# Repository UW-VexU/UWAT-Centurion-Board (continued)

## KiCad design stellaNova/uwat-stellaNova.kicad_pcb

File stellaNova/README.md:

# uwat-stellaNova, rev A

stellaNova is a VEX V5 wireless debugger. Full name: uwat-stellaNova.

It is an ESP32-S3 board that plugs into one VEX V5 smart port, receives whatever the brain writes to that port
over RS-485, and serves it to a laptop, phone or tablet over WiFi or Bluetooth LE. It can also send
commands back to the brain over the same wire (half duplex). Powered from the V5 battery through the
smart port, or from USB-C on the bench.

## What is in this folder

- The KiCad project is in this folder: open `uwat-stellaNova.kicad_pro` in KiCad 10. The project symbols
  (`stellaNova.kicad_sym`), footprints (`stellaNova.pretty/`) and 3D models (`3dmodels/`) are here too.
- `archive/uwat-stellaNova-4layer.kicad_pcb`: the original 4-layer board, kept for reference.
- `fabrication/`: **still the old 4-layer outputs. Regenerate the gerbers, drill and placement files from the 2-layer
  board before ordering.** `gerbers/` holds the files unzipped, plus the drill map PDFs.
- `bom/`: `uwat-stellaNova_revA_BOM.xlsx` (prices, order quantities, notes), `uwat-stellaNova_revA_DigiKey_upload.csv`
  (upload in DigiKey BOM Manager), plus a plain CSV BOM and a JLCPCB-style BOM.
- `docs/`: schematic PDF and PNG, layout, assembly and 3D renders, and a STEP model of the assembled board.
  The layout and 3D renders still show the 4-layer board.
- `AUDIT.md`: design audit results. `generator-scripts/`: the scripts that built the design, for reference only.

## Ordering the PCB

- Regenerate the gerbers first (see `fabrication/` above). Layers: 2. Thickness: 1.6 mm. Copper: 1 oz.
- No impedance control needed. USB here is full speed.
- Min track/spacing: the board uses 0.15 mm gaps, so pick 5/5 mil (0.127 mm) or finer.
- Min hole: 0.2 mm. The ESP32 module footprint has 0.2 mm thermal vias. Normal vias are 0.3 mm.
- Surface finish: lead-free HASL works. ENIG gives flatter pads for the ESP32 module and USB-C if hand soldering.
- Any solder mask color. Vias are tented in the files.

## Back of the board

The back reads STELLANOVA, then UWAT-VEXU F26, in Chakra Petch Bold. The font is embedded in the board
file, so the gerbers come out the same on any computer. The test pads keep their labels: TX0, RX0, VIN,
GND and 3V3, plus V5 PORT at the jack.

These notes used to be printed on the back. They live here now.

- Board: uwat-stellaNova, rev A.
- Smart port pins: 1 = A, 2 = B, 3 = GND, 4 = VBAT.
- Main parts: ESP32-S3, USB-C, RS-485.

## Board

- 48 x 40 mm, 2 layers, 1.6 mm FR4. Both layers carry signals and a GND pour. 3.3 V runs as a 0.3 mm trace,
  mostly on the back, from L1 to every 3.3 V pin. Rev A was first laid out on 4 layers with inner GND and 3.3 V
  planes. See AUDIT.md for the conversion.
- ESP32 antenna overhangs the top edge by 6 mm (Espressif's preferred placement). Keep metal 15 mm away.
- No mounting holes. The board hangs from its smart cable.
- All parts on the top side, so single-sided assembly. Test pads are on the back.
- USB-C alone gives the 500 mA USB 2.0 default. Worst case the board draws about 480 mA from it,
  so use a powered hub or the brain for long WiFi sessions. R22 keeps VBUS at 0 V on port power
  so a laptop still attaches when plugged in later.
- D5 (USB ESD protection) has its supply pin, pin 5, on 3.3 V rather than VBUS. So on port power the
  ESP32's D+ pull-up cannot lift VBUS through D5. USB and the smart cable can go in either order.
- C6 (220 uF bulk) is not fitted: the buck datasheet characterises 22 to 68 uF of output
  capacitance. Fit it only if a load-step test shows a dip on 3.3 V.

- U3 is MAX33071EASA+: its A/B pins survive +/-65 V even unpowered, so a miswired or damaged
  smart cable cannot kill it. ST3485EBDR (497-2080-1-ND, about $2.49) is a cheaper drop-in with
  the same pinout, but its bus pins are only rated 14 V.
- J1 pin field: other nets keep 0.5 mm from J1's pins (custom rule in the .kicad_dru), so a solder
  bridge on the hand-soldered jack cannot reach USB or a GPIO.
- Battery copper (VBAT_PORT and the fuse to diode link) keeps 0.5 mm from every other net ("Battery"
  net class), so a bridge or debris cannot put 14 V on an ESP32 pin.
- 3.3 V buck: the 10 uF input cap sits right across the U2 VIN and GND pins, the switch node runs
  straight out to L1, and the output caps sit next to L1. Feedback is on the far side, away from SW.
- SW1 (RESET) and SW2 (BOOT) are C&K PTS810 push buttons. Per the datasheet, pins 1 and 2 are tied
  together, pins 3 and 4 are tied together, and pressing the button joins the two pairs. The
  footprint and wiring match that.
- Do not populate parts (C6, R2, R4) have no paste openings and are left out of the placement file.
- Expansion pins: J4 (SDA on IO37, SCL on IO35), J5 (GND) and J6 (3.3 V) are 2.54 mm through-hole pins between
  the ESP32 and the microSD socket, labelled on the top silkscreen. Use them for an I2C sensor or display, or as
  UART1. Cut 4 pins from a breakaway strip and solder them when needed. The board has no I2C pull-ups. Most I2C
  breakout boards include them. If yours does not, add 4.7 k from SDA and from SCL to 3.3 V.

## Things to know when writing firmware or using it

- RS-485 echo: the receiver is always on (RE tied low), so the ESP32 hears its own transmissions on
  RX. Throw away the echoed bytes after each send, or use them to check for bus collisions.
- IO39 to IO42 go to the microSD card, so pin JTAG is not available. Use the built in USB JTAG.

## If you use JLCPCB assembly

- The BOM lists DigiKey parts. Match each line to an LCSC part in the JLCPCB tool, or hand solder.
- Check every part rotation in the JLCPCB placement preview. KiCad and JLCPCB do not always agree
  on the zero angle, especially for the ESP32 module, USB-C, the diodes and the LEDs.
- J1 (smart port jack) is through-hole. Hand solder it after assembly.

## Check before first power-up

0. Before ordering, print `docs/uwat-stellaNova-1to1-print.pdf` at 100% scale (not "fit to page")
   and set a real Molex 0955012441 jack on it (the same jack as powerJackal). Its pins and the two pegs
   must line up with the holes. If a peg does not fit, it only locates the jack, so it can be cut off.
1. Jack pin map: 1 = RS-485 A, 2 = RS-485 B, 3 = GND, 4 = battery. Contact order is A, B, GND, + as
   on the labelled smart cable photo on the VEX Forum (black A, red B, green GND, yellow +).
   VEX smart cables are straight-through.
2. On the first board, plug a smart cable into J1 and beep each wire through to the pads on the back:
   black to J1.1, red to J1.2, green to J1.3, yellow to J1.4. Also beep each button: SW1 should
   short EN to GND only while pressed, SW2 should short IO0 to GND only while pressed.
3. Power from USB-C first: 3.3 V on TP2. Then plug into the brain with USB unplugged. The PWR LED
   should light. If it does not, unplug: nothing is damaged (D2 blocks reverse, U3 is 65 V rated).
4. Scope A/B during bring-up and confirm the brain releases the bus between transmissions.
5. Load-step 3.3 V (50 to 400 mA) at 10 V and 14.6 V in. Fit C6 only if it dips.

## Firmware pin map

| Function | GPIO |
|---|---|
| RS-485 RX / DE / TX | IO9 / IO10 / IO11 (UART RS485 half-duplex mode, RTS = IO10) |
| USB D- / D+ | IO19 / IO20 (USB Serial/JTAG) |
| microSD CLK / CMD / D0 / D1 / D2 / D3 | IO40 / IO41 / IO39 / IO38 / IO2 / IO42 |
| microSD card detect | IO1 (low = card in) |
| LEDs LINK / ACT | IO13 / IO14 (high = on) |
| BOOT / RESET | IO0 / EN |
| UART0 TX / RX (back pads) | IO43 / IO44 |
| Expansion pins J4 SDA / SCL | IO37 / IO35 (any function, so they also work as UART1 TX / RX) |
| Expansion pins J5 / J6 | GND / 3.3 V |

Module is ESP32-S3-WROOM-1-N16R2: set PSRAM to Quad (QSPI) mode, not Octal. IO35 and IO37 are free only
because this module's PSRAM is quad. A module with octal PSRAM (R8 or R16V) uses those pins, so keep the N16R2.

Brain side: `vexGenericSerialEnable(port, 0)` then `vexGenericSerialBaudrate(port, 230400)`, or `pros::Serial`.

## Verification

2-layer board, checked with KiCad 10 on 2026-10-30. The report is `uwat-stellaNova-drc.rpt`.

- ERC: 0 errors.
- PCB DRC, with the J1 pin-field rule and the 0.5 mm battery rule: 0 violations, 0 unconnected.
- Schematic to PCB parity: 0 issues. Every pad is on the net the schematic gives it.
- The board file is KiCad 10 format, so KiCad 9 and older cannot open it. The schematic is still KiCad 7 format.

## BOM (DigiKey Canada, checked 2026-10-30)

| Qty | Refs | Value | MPN | DigiKey CA | Stock | CAD qty 1 |
|---|---|---|---|---|---|---|
| 1 | C1 | 10uF 50V | Samsung CL32B106KBJNNNE | 1276-3387-1-ND | 742,985 | $1.02 |
| 5 | C2 C3 C7 C9 C12 | 100nF | Yageo CC0603KRX7R9BB104 | 311-1344-1-ND | 4,044,224 | $0.21 |
| 2 | C4 C5 | 22uF | Murata GRM21BR61A226ME51L | 490-10511-1-ND | 269,759 | $0.30 |
| 2 | C8 C11 | 10uF | Murata GRM21BR61E106KA73K | 490-16824-1-ND | 88,143 | $0.25 |
| 1 | C10 | 1uF | TDK C1608X5R1H105K080AB | 445-7468-1-ND | 105,003 | $0.25 |
| 1 | C13 | 56pF | KEMET C0603C560J5GACTU | 399-C0603C560J5GACTUCT-ND | 153,858 | $0.15 |
| 1 | D1 | SMAJ18A | Bourns SMAJ18A | SMAJ18ABCT-ND | 29,489 | $0.77 |
| 2 | D2 D3 | PMEG6020ER | Nexperia PMEG6020ER,115 | 1727-5217-1-ND | 375,398 | $0.74 |
| 1 | D5 | USBLC6-2SC6 | STMicroelectronics USBLC6-2SC6 | 497-5235-1-ND | 63,343 | $0.80 |
| 1 | D6 | Green | Lite-On LTST-C191KGKT | 160-1446-1-ND | 2,712,898 | $0.24 |
| 1 | D7 | Orange | Lite-On LTST-C191KFKT | 160-1445-1-ND | 195,728 | $0.22 |
| 1 | D8 | Red | Lite-On LTST-C191KRKT | 160-1447-1-ND | 1,354,761 | $0.24 |
| 1 | F1 | PTC 0.5 A 30 V | Bel Fuse 0ZCG0050AF2C | 5923-0ZCG0050AF2CCT-ND | 345,670 | $0.31 |
| 1 | J1 | V5 smart port (4P4C) | Molex 0955012441 | WM5568-ND | 4,151 | $1.53 |
| 1 | J2 | USB-C 2.0 | GCT USB4105-GF-A | 2073-USB4105-GF-ACT-ND | 85,103 | $1.19 |
| 1 | J3 | microSD push-push | Hirose DM3AT-SF-PEJM5 | HR1964CT-ND | 76,375 | $5.27 |
| 1 | L1 | 10uH | Wurth 74438357100 | 732-11206-1-ND | 15,980 | $2.68 |
| 1 | R1 | 100k | Stackpole RMCF0603FT100K | RMCF0603FT100KCT-ND | 970,951 | $0.17 |
| 9 | R3 R5 R6 R9 R10 R11 R12 R13 R14 | 10k | Yageo RC0603FR-1310KL | 13-RC0603FR-1310KLCT-ND | 221,620 | $0.16 |
| 3 | R7 R8 R22 | 5.1k | Yageo RC0603FR-075K1L | 311-5.10KHRCT-ND | 405,843 | $0.16 |
| 3 | R15 R16 R17 | 1k | Yageo RC0603FR-071KL | 311-1.00KHRCT-ND | 1,993,948 | $0.17 |
| 2 | R18 R19 | 22 | Stackpole RMCF0603FT22R0 | RMCF0603FT22R0CT-ND | 2,171,898 | $0.16 |
| 1 | R20 | 93.1k | Stackpole RMCF0603FT93K1 | RMCF0603FT93K1CT-ND | 216,165 | $0.16 |
| 1 | R21 | 30.1k | Yageo RC0603FR-0730K1L | 311-30.1KHRCT-ND | 119,797 | $0.16 |
| 2 | SW1 SW2 | Tactile | C&K PTS810 SJM 250 SMTR LFS | CKN10502CT-ND | 69,851 | $0.92 |
| 1 | U1 | ESP32-S3-WROOM-1-N16R2 | Espressif ESP32-S3-WROOM-1-N16R2 | 5407-ESP32-S3-WROOM-1-N16R2CT-ND | 4,702 | $10.61 |
| 1 | U2 | AP63301WU-7 | Diodes Inc AP63301WU-7 | 31-AP63301WU-7CT-ND | 13,846 | $1.52 |
| 1 | U3 | MAX33071EASA+ | Analog Devices MAX33071EASA+ | 505-MAX33071EASA+-ND | 2,956 | $12.30 |
| 4 pins | J4 J5 J6 | Header pins, 2.54 mm | Sullins PRPC040SAAN-RC (40-pin strip, one covers 10 boards) | S1011EC-40-ND | 65,709 | $1.83 per strip |

Do not populate: C6 R2 R4

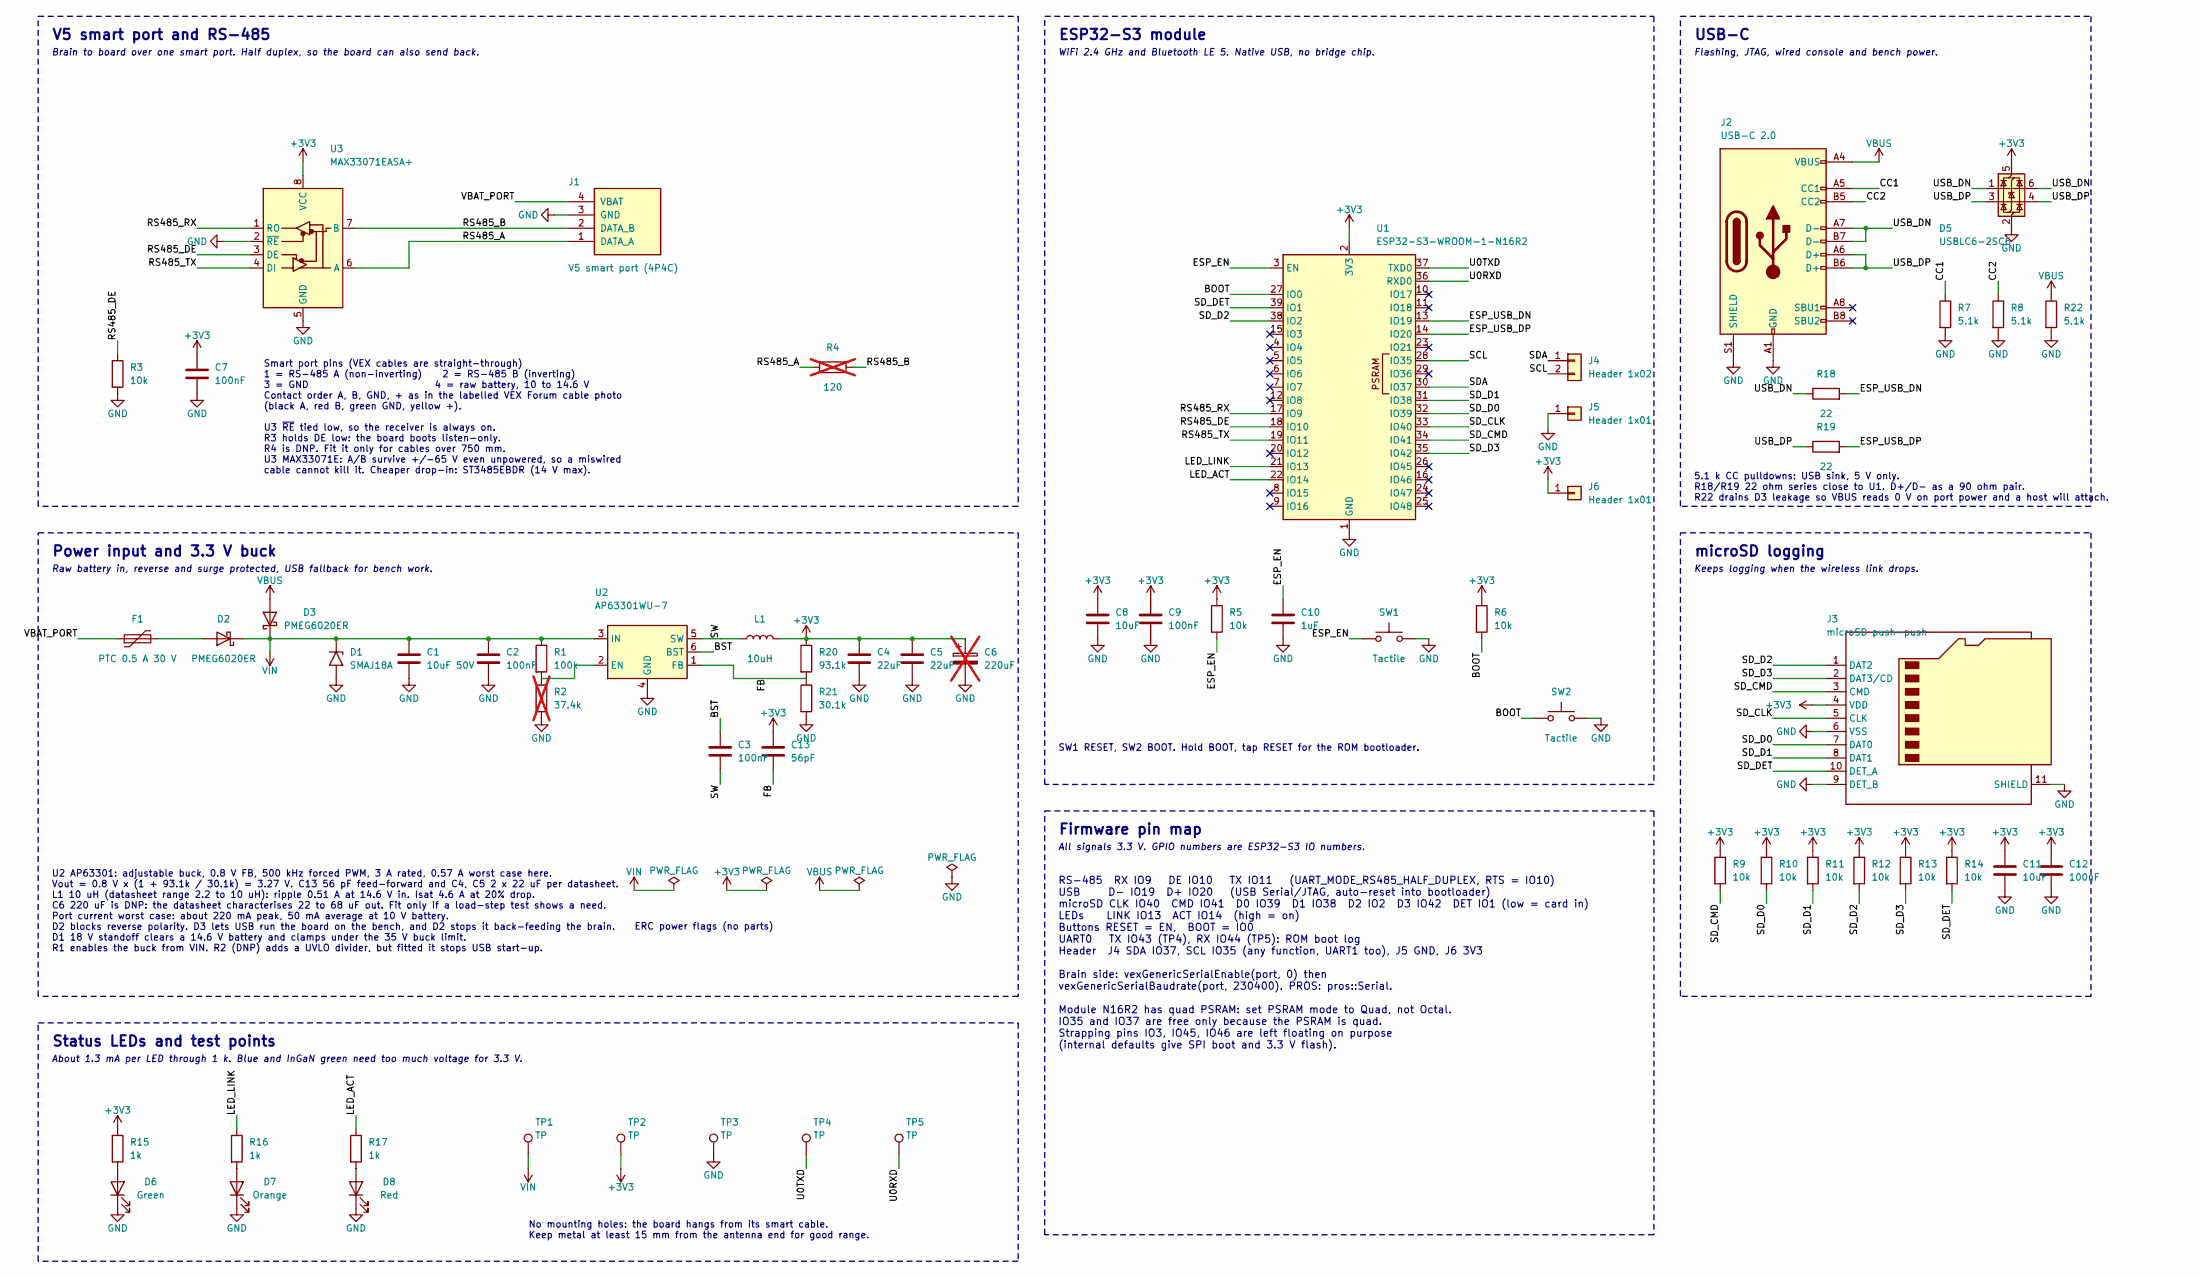
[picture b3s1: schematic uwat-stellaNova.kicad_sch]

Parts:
C1: 10uF 50V; C_1210_3225Metric; MPN CL32B106KBJNNNE; DigiKey 1276-3387-1-ND
C2, C3, C7, C9, C12: 100nF; C_0603_1608Metric; MPN CC0603KRX7R9BB104; DigiKey 311-1344-1-ND
C4, C5: 22uF; C_0805_2012Metric; MPN GRM21BR61A226ME51L; DigiKey 490-10511-1-ND
C6: 220uF; CP_EIA-3528-21_Kemet-B; MPN T520B227M006ATE045; DigiKey 399-5755-1-ND; not fitted
C8, C11: 10uF; C_0805_2012Metric; MPN GRM21BR61E106KA73K; DigiKey 490-16824-1-ND
C10: 1uF; C_0603_1608Metric; MPN C1608X5R1H105K080AB; DigiKey 445-7468-1-ND
C13: 56pF; C_0603_1608Metric; MPN C0603C560J5GACTU; DigiKey 399-C0603C560J5GACTUCT-ND
D1: SMAJ18A; D_SMA; MPN SMAJ18A; DigiKey SMAJ18ABCT-ND
D2, D3: PMEG6020ER; Nexperia_CFP3_SOD-123W; MPN PMEG6020ER,115; DigiKey 1727-5217-1-ND
D5: USBLC6-2SC6; SOT-23-6; MPN USBLC6-2SC6; DigiKey 497-5235-1-ND
D6: Green; LED_0603_1608Metric; MPN LTST-C191KGKT; DigiKey 160-1446-1-ND
D7: Orange; LED_0603_1608Metric; MPN LTST-C191KFKT; DigiKey 160-1445-1-ND
D8: Red; LED_0603_1608Metric; MPN LTST-C191KRKT; DigiKey 160-1447-1-ND
F1: PTC 0.5 A 30 V; Fuse_1812_4532Metric; MPN 0ZCG0050AF2C; DigiKey 5923-0ZCG0050AF2CCT-ND
J1: V5 smart port (4P4C); Molex_95501-2441_4P4C_Horizontal; MPN 0955012441; DigiKey WM5568-ND
J2: USB-C 2.0; USB_C_Receptacle_GCT_USB4105-xx-A_16P_TopMnt_Horizontal; MPN USB4105-GF-A; DigiKey 2073-USB4105-GF-ACT-ND
J3: microSD push-push; microSD_HC_Hirose_DM3AT-SF-PEJM5; MPN DM3AT-SF-PEJM5; DigiKey HR1964CT-ND
J4: Header 1x02; PinHeader_1x02_P2.54mm_Vertical_Compact; MPN PRPC040SAAN-RC; DigiKey S1011EC-40-ND
J5, J6: Header 1x01; PinHeader_1x01_P2.54mm_Vertical_Compact; MPN PRPC040SAAN-RC; DigiKey S1011EC-40-ND
L1: 10uH; L_Wuerth_MAPI-4030; MPN 74438357100; DigiKey 732-11206-1-ND
R1: 100k; R_0603_1608Metric; MPN RMCF0603FT100K; DigiKey RMCF0603FT100KCT-ND
R2: 37.4k; R_0603_1608Metric; MPN RC0603FR-0737K4L; DigiKey 311-37.4KHRCT-ND; not fitted
R3, R5, R6, R9, R10, R11, R12, R13, R14: 10k; R_0603_1608Metric; MPN RC0603FR-1310KL; DigiKey 13-RC0603FR-1310KLCT-ND
R4: 120; R_0603_1608Metric; MPN RC0603FR-07120RL; DigiKey 311-120HRCT-ND; not fitted
R7, R8, R22: 5.1k; R_0603_1608Metric; MPN RC0603FR-075K1L; DigiKey 311-5.10KHRCT-ND
R15, R16, R17: 1k; R_0603_1608Metric; MPN RC0603FR-071KL; DigiKey 311-1.00KHRCT-ND
R18, R19: 22; R_0603_1608Metric; MPN RMCF0603FT22R0; DigiKey RMCF0603FT22R0CT-ND
R20: 93.1k; R_0603_1608Metric; MPN RMCF0603FT93K1; DigiKey RMCF0603FT93K1CT-ND
R21: 30.1k; R_0603_1608Metric; MPN RC0603FR-0730K1L; DigiKey 311-30.1KHRCT-ND
SW1, SW2: Tactile; SW_SPST_PTS810; MPN PTS810 SJM 250 SMTR LFS; DigiKey CKN10502CT-ND
TP1, TP2, TP3, TP4, TP5: TP; TestPoint_Pad_D1.5mm
U1: ESP32-S3-WROOM-1-N16R2; ESP32-S3-WROOM-1; MPN ESP32-S3-WROOM-1-N16R2; DigiKey 5407-ESP32-S3-WROOM-1-N16R2CT-ND
U2: AP63301WU-7; TSOT-23-6; MPN AP63301WU-7; DigiKey 31-AP63301WU-7CT-ND
U3: MAX33071EASA+; SOIC-8_3.9x4.9mm_P1.27mm; MPN MAX33071EASA+; DigiKey 505-MAX33071EASA+-ND

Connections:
+3V3: C4.1, C5.1, C6.1, C7.1, C8.1, C9.1, C11.1, C12.1, C13.1, D5.5 (VBUS), J3.4 (VDD), J6.1, L1.2, R5.1, R6.1, R9.1, R10.1, R11.1, R12.1, R13.1, R14.1, R15.1, R20.1, TP2.1, U1.2 (3V3), U3.8 (VCC)
/BOOT: R6.2, SW2.1, U1.27 (IO0)
/BST: C3.1, U2.6 (BST)
/CC1: J2.A5 (CC1), R7.1
/CC2: J2.B5 (CC2), R8.1
/ESP_EN: C10.1, R5.2, SW1.1, U1.3 (EN)
/ESP_USB_DN: R18.2, U1.13 (IO19)
/ESP_USB_DP: R19.2, U1.14 (IO20)
/FB: C13.2, R20.2, R21.1, U2.1 (FB)
/LED_ACT: R17.1, U1.22 (IO14)
/LED_LINK: R16.1, U1.21 (IO13)
/RS485_A: J1.1 (DATA_A), R4.1, U3.6 (A)
/RS485_B: J1.2 (DATA_B), R4.2, U3.7 (B)
/RS485_DE: R3.1, U1.18 (IO10), U3.3 (DE)
/RS485_RX: U1.17 (IO9), U3.1 (RO)
/RS485_TX: U1.19 (IO11), U3.4 (DI)
/SCL: J4.2, U1.28 (IO35)
/SDA: J4.1, U1.30 (IO37)
/SD_CLK: J3.5 (CLK), U1.33 (IO40)
/SD_CMD: J3.3 (CMD), R9.2, U1.34 (IO41)
/SD_D0: J3.7 (DAT0), R10.2, U1.32 (IO39)
/SD_D1: J3.8 (DAT1), R11.2, U1.31 (IO38)
/SD_D2: J3.1 (DAT2), R12.2, U1.38 (IO2)
/SD_D3: J3.2 (DAT3/CD), R13.2, U1.35 (IO42)
/SD_DET: J3.10 (DET_A), R14.2, U1.39 (IO1)
/SW: C3.2, L1.1, U2.5 (SW)
/U0RXD: TP5.1, U1.36 (RXD0)
/U0TXD: TP4.1, U1.37 (TXD0)
/USB_DN: D5.1 (I/O1), D5.6 (I/O1), J2.A7 (D-), J2.B7 (D-), R18.1
/USB_DP: D5.3 (I/O2), D5.4 (I/O2), J2.A6 (D+), J2.B6 (D+), R19.1
/VBAT_PORT: F1.1, J1.4 (VBAT)
GND: C1.2, C2.2, C4.2, C5.2, C6.2, C7.2, C8.2, C9.2, C10.2, C11.2, C12.2, D1.2 (A2), D5.2 (GND), D6.1 (K), D7.1 (K), D8.1 (K), J1.3 (GND), J2.A1 (GND), J2.A12 (GND), J2.B1 (GND), J2.B12 (GND), J2.S1 (SHIELD), J3.6 (VSS), J3.9 (DET_B), J3.11 (SHIELD), J5.1, R2.2, R3.2, R7.2, R8.2, R21.2, R22.2, SW1.2, SW2.2, TP3.1, U1.1 (GND), U1.40 (GND), U1.41 (GND), U2.4 (GND), U3.2 (~RE), U3.5 (GND)
unnamed: D2.2 (A), F1.2
unnamed: D6.2 (A), R15.2
unnamed: D7.2 (A), R16.2
unnamed: D8.2 (A), R17.2
unnamed: R1.2, R2.1, U2.2 (EN)
VBUS: D3.2 (A), J2.A4 (VBUS), J2.A9 (VBUS), J2.B4 (VBUS), J2.B9 (VBUS), R22.1
VIN: C1.1, C2.1, D1.1 (A1), D2.1 (K), D3.1 (K), R1.1, TP1.1, U2.3 (IN)

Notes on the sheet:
V5 smart port and RS-485
Brain to board over one smart port. Half duplex, so the board can also send back.
Smart port pins (VEX cables are straight-through) 1 = RS-485 A (non-inverting) 2 = RS-485 B (inverting) 3 = GND 4 = raw battery, 10 to 14.6 V Contact order A, B, GND, + as in the labelled VEX Forum cable photo (black A, red B, green GND, yellow +). U3 ~{RE} tied low, so the receiver is always on. R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
Power input and 3.3 V buck
Raw battery in, reverse and surge protected, USB fallback for bench work.
ERC power flags (no parts)
U2 AP63301: adjustable buck, 0.8 V FB, 500 kHz forced PWM, 3 A rated, 0.57 A worst case here. Vout = 0.8 V x (1 + 93.1k / 30.1k) = 3.27 V. C13 56 pF feed-forward and C4, C5 2 x 22 uF per datasheet. L1 10 uH (datasheet range 2.2 to 10 uH): ripple 0.51 A at 14.6 V in. Isat 4.6 A at 20% drop. C6 220 u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
ESP32-S3 module
WiFi 2.4 GHz and Bluetooth LE 5. Native USB, no bridge chip.
SW1 RESET, SW2 BOOT. Hold BOOT, tap RESET for the ROM bootloader.
USB-C
Flashing, JTAG, wired console and bench power.
5.1 k CC pulldowns: USB sink, 5 V only. R18/R19 22 ohm series close to U1. D+/D- as a 90 ohm pair. R22 drains D3 leakage so VBUS reads 0 V on port power and a host will attach.
microSD logging
Keeps logging when the wireless link drops.
Status LEDs and test points
About 1.3 mA per LED through 1 k. Blue and InGaN green need too much voltage for 3.3 V.
No mounting holes: the board hangs from its smart cable. Keep metal at least 15 mm from the antenna end for good range.
Firmware pin map
All signals 3.3 V. GPIO numbers are ESP32-S3 IO numbers.
RS-485 RX IO9 DE IO10 TX IO11 (UART_MODE_RS485_HALF_DUPLEX, RTS = IO10) USB D- IO19 D+ IO20 (USB Serial/JTAG, auto-reset into bootloader) microSD CLK IO40 CMD IO41 D0 IO39 D1 IO38 D2 IO2 D3 IO42 DET IO1 (low = card in) LEDs LINK IO13 ACT IO14 (high = on) Buttons RESET = EN, BOOT = IO0 UART0 TX IO43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

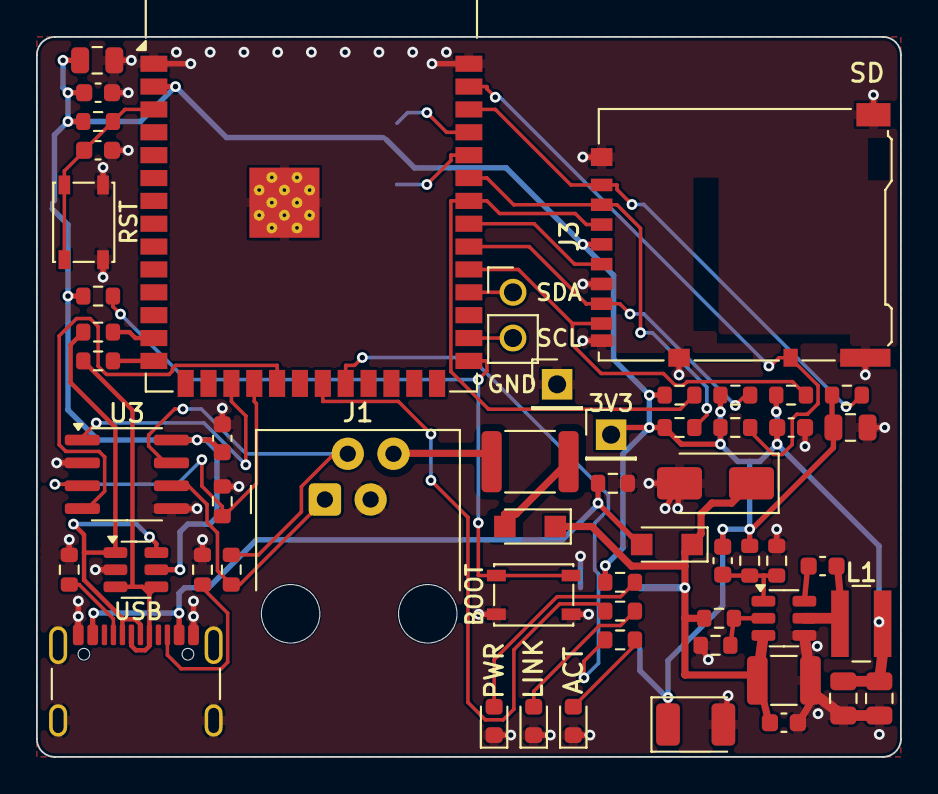
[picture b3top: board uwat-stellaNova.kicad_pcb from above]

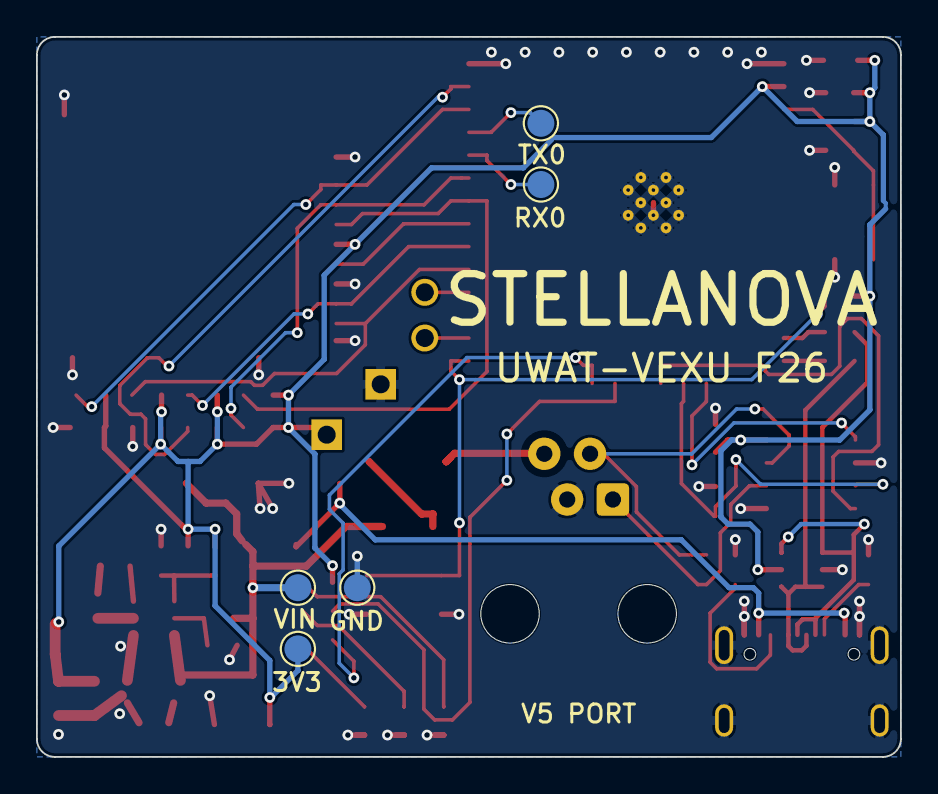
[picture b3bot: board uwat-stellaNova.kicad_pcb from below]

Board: 2 copper layers, 48.0 x 40.0 mm, 60 parts (5 on the bottom side), 39 nets.

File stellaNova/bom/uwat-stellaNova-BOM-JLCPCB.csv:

Comment,Designator,Footprint,MPN
10uF 50V,C1,C_1210_3225Metric,CL32B106KBJNNNE
100nF,"C2,C3,C7,C9,C12",C_0603_1608Metric,CC0603KRX7R9BB104
22uF,"C4,C5",C_0805_2012Metric,GRM21BR61A226ME51L
10uF,"C8,C11",C_0805_2012Metric,GRM21BR61E106KA73K
1uF,C10,C_0603_1608Metric,C1608X5R1H105K080AB
56pF,C13,C_0603_1608Metric,C0603C560J5GACTU
SMAJ18A,D1,D_SMA,SMAJ18A
PMEG6020ER,"D2,D3",Nexperia_CFP3_SOD-123W,"PMEG6020ER,115"
USBLC6-2SC6,D5,SOT-23-6,USBLC6-2SC6
Green,D6,LED_0603_1608Metric,LTST-C191KGKT
Orange,D7,LED_0603_1608Metric,LTST-C191KFKT
Red,D8,LED_0603_1608Metric,LTST-C191KRKT
PTC 0.5 A 30 V,F1,Fuse_1812_4532Metric,0ZCG0050AF2C
V5 smart port (4P4C),J1,Molex_95501-2441_4P4C_Horizontal,0955012441
USB-C 2.0,J2,USB_C_Receptacle_GCT_USB4105-xx-A_16P_TopMnt_Horizontal,USB4105-GF-A
microSD push-push,J3,microSD_HC_Hirose_DM3AT-SF-PEJM5,DM3AT-SF-PEJM5
10uH,L1,L_Wuerth_MAPI-4030,74438357100
100k,R1,R_0603_1608Metric,RMCF0603FT100K
10k,"R3,R5,R6,R9,R10,R11,R12,R13,R14",R_0603_1608Metric,RC0603FR-1310KL
5.1k,"R7,R8,R22",R_0603_1608Metric,RC0603FR-075K1L
1k,"R15,R16,R17",R_0603_1608Metric,RC0603FR-071KL
22,"R18,R19",R_0603_1608Metric,RMCF0603FT22R0
93.1k,R20,R_0603_1608Metric,RMCF0603FT93K1
30.1k,R21,R_0603_1608Metric,RC0603FR-0730K1L
Tactile,"SW1,SW2",SW_SPST_PTS810,PTS810 SJM 250 SMTR LFS
ESP32-S3-WROOM-1-N16R2,U1,ESP32-S3-WROOM-1,ESP32-S3-WROOM-1-N16R2
AP63301WU-7,U2,TSOT-23-6,AP63301WU-7
MAX33071EASA+,U3,SOIC-8_3.9x4.9mm_P1.27mm,MAX33071EASA+
Header 1x02,J4,PinHeader_1x02_P2.54mm_Vertical_Compact,PRPC040SAAN-RC
Header 1x01,"J5,J6",PinHeader_1x01_P2.54mm_Vertical_Compact,PRPC040SAAN-RC

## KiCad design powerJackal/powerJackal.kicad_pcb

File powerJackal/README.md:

# powerJackal: smart port power test board, rev A

A small test board for the UWAT VEXU Centurion boards. It plugs into a VEX V5 smart port (or a bench supply), makes 5 V and 3.3 V, and measures the port input, the 5 V rail and the 3.3 V rail with three INA226 monitors. An ESP32-C3 module reads the monitors over I2C and reports over the USB-C port. An OLED can plug into the STEMMA QT connector.

## Status

Rev A design files. The KiCad design rule check shows 0 errors and 0 unconnected items, and the schematic netlist matches the board. Not built or tested yet. See [Before ordering](#before-ordering) for the checks still open.

## Board at a glance

| | |
|---|---|
| Size | 72.4 x 47.0 mm, 1.5 mm corner radius |
| Stackup | 2 layers, 1.6 mm FR-4, 1 oz copper |
| Mounting | 4 x 4.5 mm holes for #8-32 screws, 63.5 x 38.1 mm apart on the VEX 0.5 in grid, 4.45 mm from the edges |
| Parts | 59 placed parts, all on the top side, plus 9 bare copper test pads |
| Cost | About $63.53 CAD in parts per board at DigiKey Canada qty-1 prices, plus $6.26 for the J6 and J9 plugs. A parts order for 2 boards with spares is about $153.35 CAD at DigiKey's price breaks (checked October 29, 2026). Bare PCB not included |
| Inputs | J1 smart port (11 to 14.4 V battery), J2 bench supply 10 to 15 V |
| Outputs | J6 5 V up to 2 A, J9 3.3 V, J3 STEMMA QT (I2C + 3.3 V) |
| MCU | ESP32-C3-MINI-1U-N4X, USB serial and JTAG on USB-C |

## Folder map

| Path | What it is |
|---|---|
| `powerJackal.kicad_pro`, `.kicad_sch`, `.kicad_pcb`, `.kicad_dru` | The KiCad project. Open the `.kicad_pro` file |
| `fp-lib-table`, `sym-lib-table` | Point KiCad at the project library in `lib/` |
| `lib/` | Project library: UWAT symbols, footprints and the ESP32 3D model |
| `fab/revA/` | Gerbers and drill files (zip) plus the pick-and-place file |
| `bom/` | BOM spreadsheet with formulas, and a CSV for DigiKey BOM Manager |
| `docs/powerJackal_revA_schematic.pdf` | Schematic as a PDF |
| `docs/design_notes.md` | How the board works, layout rules, test plan, revision history |
| `docs/firmware.md` | Firmware specification: pins, INA226 setup, expected readings, limits, features to code |
| `docs/board_viewer/` | Interactive board page (3D, assembly, copper, schematic, BOM). Open the `.html` file in a browser |
| `docs/powerJackal_wiring_map.html` | Pin-by-pin wiring map of every part |
| `docs/images/` | Pictures that explain design changes |
| `tools/` | The Python scripts that generated rev A, plus layout checkers. See `tools/README.md` |
| `CLAUDE.md` | Instructions for Claude Code when working in this folder |

## Opening the project

1. Open `powerJackal.kicad_pro` in KiCad.
2. The board file is KiCad 10.0 format. It was saved with KiCad 10 for the rev A fixes, so KiCad 9 and older cannot open it. The schematic is still KiCad 7.0 format, and KiCad 10 upgrades it when you save. Commit a format upgrade by itself so the diff stays readable.
3. The UWAT library loads from `lib/` through the project library tables, so nothing needs to be installed. Everything else uses KiCad's standard libraries.
4. Many tracks are locked to protect the hand routing. Unlock a track (select it, then press L) before moving it.

## How it works, in short

- **Power in:** the smart port (J1) and the bench input (J2) each pass through a Schottky diode (D5, D3), so either can be plugged in alone or both at once. Then a 1.5 A polyfuse (F1), the input shunt R1, a TVS clamp (D1) and bulk capacitors.
- **5 V:** TI TPSM53602 step-down module (U1), up to 2 A. Shunt R2 measures the 5 V rail.
- **3.3 V:** MCP1826S LDO (U6), fed from the 5 V rail through D2. Shunt R12 measures the 3.3 V rail.
- **USB power switch:** Q1 (AO3401A) lets USB power the 3.3 V side only while the 5 V rail is off. On the desk, USB alone runs the ESP32 for flashing. With port or bench power on, USB only carries data, so the port readings never include USB current.
- **Measurement:** three INA226 monitors on one I2C bus.

| Monitor | Measures | I2C address | Shunt | Full scale |
|---|---|---|---|---|
| U2 | Port input, after F1 | 0x40 | R1, 20 mΩ | about 4 A |
| U3 | 5 V rail | 0x41 | R2, 20 mΩ | about 4 A |
| U5 | 3.3 V rail | 0x45 | R12, 50 mΩ | about 1.6 A |

## Quick reference

These notes used to be printed on the back of the board. They live here now.

- **Smart port pinout:** check the J1 pinout with a meter before the first plug-in.
- **USB-C:** flashes the ESP32-C3 and carries its serial output.
- **Stuck?** Hold BOOT, tap RESET, then let go of BOOT.
- **USB power:** USB powers the 3.3 V side only while port and bench power are off.
- **INA226 addresses:** 0x40 port input, 0x41 5 V rail, 0x45 3.3 V rail.

## Firmware quick start

- **Arduino IDE:** board "ESP32C3 Dev Module", set USB CDC On Boot to Enabled.
- **I2C:** `Wire.begin(4, 5)` (SDA GPIO4, SCL GPIO5). External 4.7 kΩ pull-ups are on the board.
- **Other pins:** status LED on GPIO10, PGOOD (5 V good) on GPIO3, active high.
- **INA226 calibration:** use a current LSB of 125 µA and CAL = 2048 for U2 and U3. Use 50 µA and CAL = 2048 for U5. The power LSB is 25 x the current LSB.
- **Recovery:** if a firmware bug breaks USB, hold BOOT (SW2), tap RESET (SW1), then let go of BOOT. The chip starts in its ROM download mode, which always works over USB.
- **Radio:** keep Wi-Fi and Bluetooth off. No antenna is fitted.

The full ESP32 pin map is in [docs/design_notes.md](docs/design_notes.md#esp32-c3-pins). The firmware specification, with what to build and the readings to expect, is in [docs/firmware.md](docs/firmware.md).

## Ordering boards

1. **Fab:** upload `fab/revA/powerJackal_revA_gerbers.zip` to the board house.
   - 2 layers, 1.6 mm, 1 oz copper, any solder mask color.
   - Tented vias. Ask them to tent or plug the vias in U1's exposed pad if they offer it.
2. **Parts:** upload `bom/powerJackal_revA_DigiKey_upload.csv` to BOM Manager on digikey.ca.
   - Set the number of boards in the yellow cell of the spreadsheet first. Quantities include spares.
   - To buy a different quantity of a part, type it in the yellow Your order qty column. The unit price follows DigiKey's price breaks, and the Tip column shows when buying up to the next break costs less.
   - After changing quantities, save the DigiKey upload tab as CSV and upload that instead.
3. **Assembly:** `fab/revA/powerJackal_revA_positions_top.csv` gives part centers in mm from the bottom-left board corner, top side only.

## Before ordering

- **J1 pinout:** check the smart port pinout with a meter on a powered brain. The board assumes yellow = power, green = GND, red = RS-485 B, black = RS-485 A.
- **J1 footprint:** this is a placeholder until it is checked against the Molex 0955012441 drawing. Test-fit a real VEX smart cable.
- **Port current:** VEX publishes no rating for the port power pin. Keep the added load at 20 W or less (about 1.6 A at 12.8 V). This board pulls about 12 W with 2 A on the 5 V rail.

## Regenerating outputs after a change

Run these from this folder. On Windows, use the KiCad Command Prompt, or call `kicad-cli.exe` from the KiCad `bin` folder.

```
kicad-cli pcb drc -o drc.rpt powerJackal.kicad_pcb
kicad-cli sch export pdf -o docs/powerJackal_revA_schematic.pdf powerJackal.kicad_sch
kicad-cli pcb export gerbers -l F.Cu,B.Cu,F.Paste,B.Paste,F.Silkscreen,B.Silkscreen,F.Mask,B.Mask,Edge.Cuts --subtract-soldermask --use-drill-file-origin -o fab/revA/gerbers/ powerJackal.kicad_pcb
kicad-cli pcb export drill --excellon-separate-th --drill-origin plot -o fab/revA/gerbers/ powerJackal.kicad_pcb
kicad-cli pcb export pos --format csv --units mm --side front --use-drill-file-origin -o fab/revA/powerJackal_revA_positions_top.csv powerJackal.kicad_pcb
```

Then zip the `fab/revA/gerbers/` folder into `powerJackal_revA_gerbers.zip`. If the board changes after rev A is ordered, put the new outputs in `fab/revB/` and keep `revA` as it was sent.

## Online copies

Private claude.ai pages with the same content as `docs/`. Share them from claude.ai before posting the links to the team.

- Board viewer: https://claude.ai/artifact/YNZmFietXBuHHMfKenqW3t
- Wiring map: https://claude.ai/artifact/1g2pL9suJduEafN7xD549V

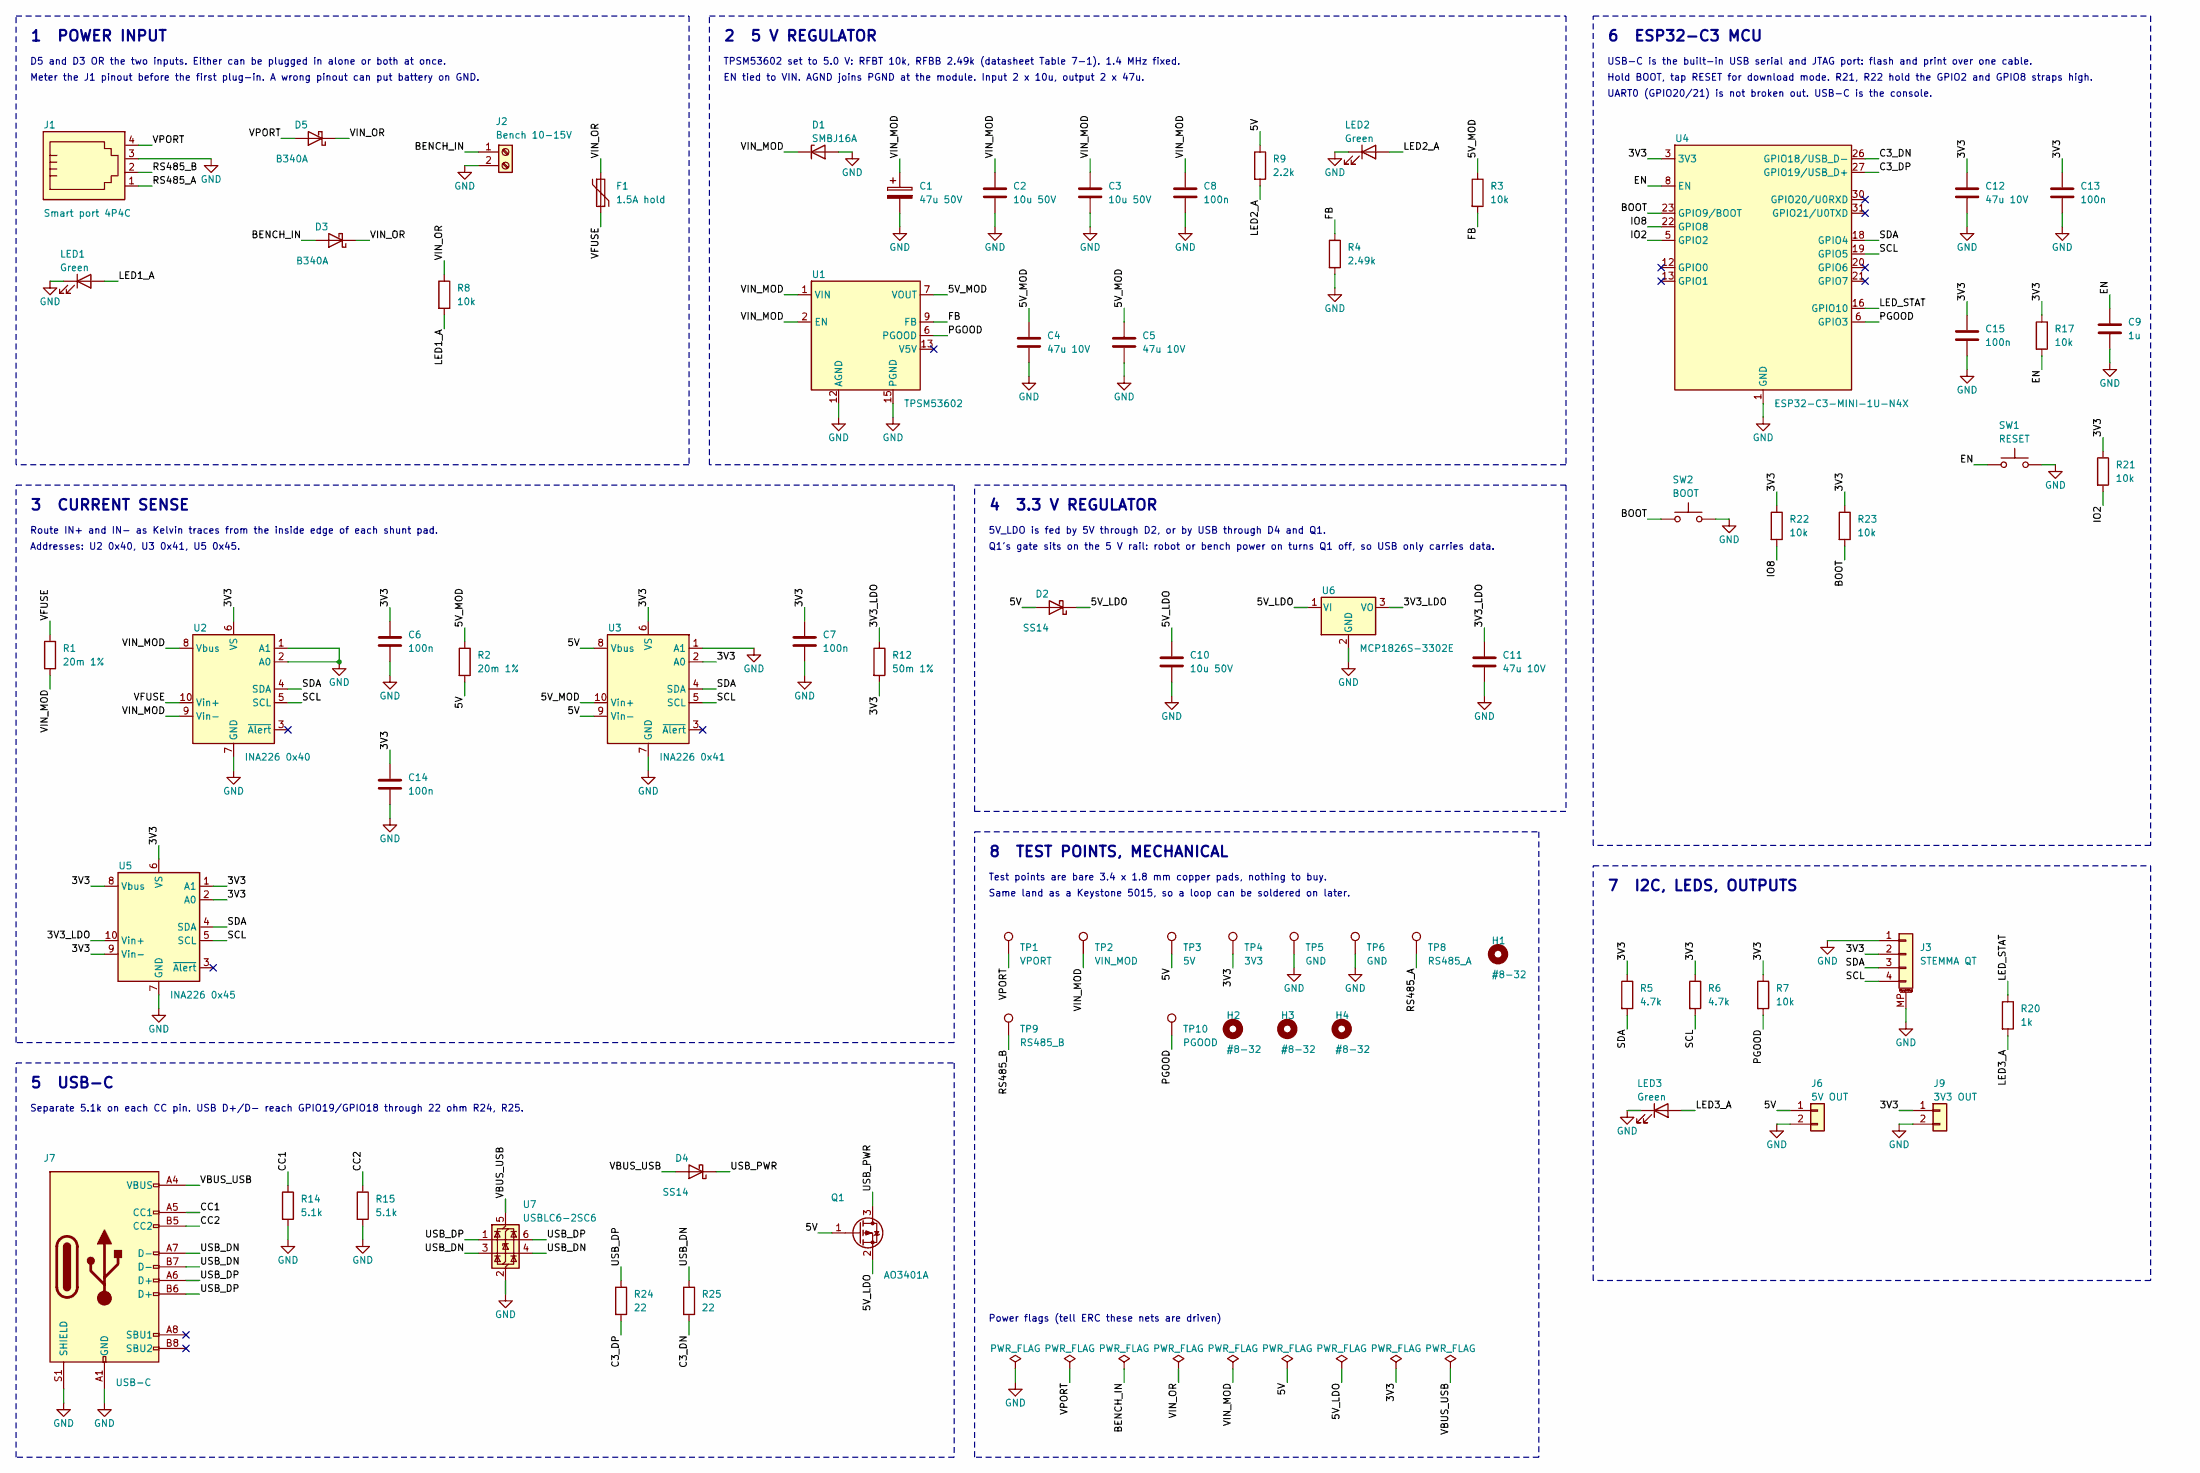
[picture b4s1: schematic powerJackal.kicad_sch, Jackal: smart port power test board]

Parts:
C1: 47u 50V; CP_Radial_D6.3mm_P2.50mm; MPN EEU-FR1H470
C2, C3, C10: 10u 50V; C_1210_3225Metric; MPN CL32B106KBJNNNE
C4, C5, C11, C12: 47u 10V; C_1206_3216Metric; MPN GRM31CR61A476ME15L
C6, C7, C8, C13, C14, C15: 100n; C_0805_2012Metric; MPN CC0805KRX7R9BB104
C9: 1u; C_0805_2012Metric; MPN CC0805KKX7R8BB105
D1: SMBJ16A; D_SMB; MPN SMBJ16A
D2, D4: SS14; D_SMA; MPN SS14-E3/61T
D3, D5: B340A; D_SMA; MPN B340A-13-F
F1: 1.5A hold; Fuse_Littelfuse_2016L; MPN 2016L150/33DR
H1, H2, H3, H4: #8-32; MountingHole_4.5mm_8-32
J1: Smart port 4P4C; Molex_95501-2441_4P4C_Horizontal; MPN 0955012441
J2: Bench 10-15V; TerminalBlock_Phoenix_MKDS-1,5-2-5.08_1x02_P5.08mm_Horizont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; MPN 1935161
J3: STEMMA QT; JST_SH_SM04B-SRSS-TB_1x04-1MP_P1.00mm_Horizontal; MPN SM04B-SRSS-TB
J6: 5V OUT; PhoenixContact_MC_1,5_2-G-3.81_1x02_P3.81mm_Horizontal; MPN 1803277
J7: USB-C; USB_C_Receptacle_GCT_USB4105-xx-A_16P_TopMnt_Horizontal; MPN USB4105-GF-A
J9: 3V3 OUT; PhoenixContact_MC_1,5_2-G-3.81_1x02_P3.81mm_Horizontal; MPN 1803277
LED1, LED2, LED3: Green; LED_0805_2012Metric; MPN LTST-C171GKT
Q1: AO3401A; SOT-23; MPN AO3401A
R1, R2: 20m 1%; R_1206_3216Metric; MPN WSL1206R0200FEA
R3, R7, R8, R17, R21, R22, R23: 10k; R_0805_2012Metric; MPN RC0805FR-0710KL
R4: 2.49k; R_0805_2012Metric; MPN RC0805FR-072K49L
R5, R6: 4.7k; R_0805_2012Metric; MPN RC0805FR-074K7L
R9: 2.2k; R_0805_2012Metric; MPN RC0805FR-072K2L
R12: 50m 1%; R_1206_3216Metric; MPN WSL1206R0500FEA
R14, R15: 5.1k; R_0805_2012Metric; MPN RMCF0805FT5K10
R20: 1k; R_0805_2012Metric; MPN RC0805FR-071KL
R24, R25: 22; R_0805_2012Metric; MPN RC0805FR-0722RL
SW1: RESET; SW_SPST_TL3342; MPN TL3342F160QG
SW2: BOOT; SW_SPST_TL3342; MPN TL3342F160QG
TP1: VPORT; TestPad_3.4x1.8mm
TP2: VIN_MOD; TestPad_3.4x1.8mm
TP3: 5V; TestPad_3.4x1.8mm
TP4: 3V3; TestPad_3.4x1.8mm
TP5, TP6: GND; TestPad_3.4x1.8mm
TP8: RS485_A; TestPad_3.4x1.8mm
TP9: RS485_B; TestPad_3.4x1.8mm
TP10: PGOOD; TestPad_3.4x1.8mm
U1: TPSM53602; Texas_B3QFN-14-1EP_5x5.5mm_P0.65mm_ThermalVia; MPN TPSM53602RDAR
U2: INA226 0x40; VSSOP-10_3x3mm_P0.5mm; MPN INA226AIDGSR
U3: INA226 0x41; VSSOP-10_3x3mm_P0.5mm; MPN INA226AIDGSR
U4: ESP32-C3-MINI-1U-N4X; ESP32-C3-MINI-1U; MPN ESP32-C3-MINI-1U-N4X
U5: INA226 0x45; VSSOP-10_3x3mm_P0.5mm; MPN INA226AIDGSR
U6: MCP1826S-3302E; SOT-223-3_TabPin2; MPN MCP1826ST-3302E/DB
U7: USBLC6-2SC6; SOT-23-6; MPN USBLC6-2SC6

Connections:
/3V3: C6.1, C7.1, C12.1, C13.1, C14.1, C15.1, J3.2, J9.1, R5.1, R6.1, R7.1, R12.2, R17.1, R21.1, R22.1, R23.1, TP4.1, U2.6 (VS), U3.2 (A0), U3.6 (VS), U4.3 (3V3), U5.1 (A1), U5.2 (A0), U5.6 (VS), U5.8 (Vbus), U5.9 (Vin-)
/3V3_LDO: C11.1, R12.1, U5.10 (Vin+), U6.3 (VO)
/5V: D2.2 (A), J6.1, Q1.1 (G), R2.2, R9.1, TP3.1, U3.8 (Vbus), U3.9 (Vin-)
/5V_LDO: C10.1, D2.1 (K), Q1.2 (S), U6.1 (VI)
/5V_MOD: C4.1, C5.1, R2.1, R3.1, U1.7 (VOUT), U1.8 (VOUT), U3.10 (Vin+)
/BENCH_IN: D3.2 (A), J2.1
/BOOT: R23.2, SW2.1, U4.23 (GPIO9/BOOT)
/C3_DN: R25.2, U4.26 (GPIO18/USB_D-)
/C3_DP: R24.2, U4.27 (GPIO19/USB_D+)
/CC1: J7.A5 (CC1), R14.1
/CC2: J7.B5 (CC2), R15.1
/EN: C9.1, R17.2, SW1.1, U4.8 (EN)
/FB: R3.2, R4.1, U1.9 (FB)
/IO2: R21.2, U4.5 (GPIO2)
/IO8: R22.2, U4.22 (GPIO8)
/LED1_A: LED1.2 (A), R8.2
/LED2_A: LED2.2 (A), R9.2
/LED3_A: LED3.2 (A), R20.2
/LED_STAT: R20.1, U4.16 (GPIO10)
/PGOOD: R7.2, TP10.1, U1.6 (PGOOD), U4.6 (GPIO3)
/RS485_A: J1.1, TP8.1
/RS485_B: J1.2, TP9.1
/SCL: J3.4, R6.2, U2.5 (SCL), U3.5 (SCL), U4.19 (GPIO5), U5.5 (SCL)
/SDA: J3.3, R5.2, U2.4 (SDA), U3.4 (SDA), U4.18 (GPIO4), U5.4 (SDA)
/USB_DN: J7.A7 (D-), J7.B7 (D-), R25.1, U7.3 (I/O2), U7.4 (I/O2)
/USB_DP: J7.A6 (D+), J7.B6 (D+), R24.1, U7.1 (I/O1), U7.6 (I/O1)
/USB_PWR: D4.1 (K), Q1.3 (D)
/VBUS_USB: D4.2 (A), J7.A4 (VBUS), J7.A9 (VBUS), J7.B4 (VBUS), J7.B9 (VBUS), U7.5 (VBUS)
/VFUSE: F1.2, R1.1, U2.10 (Vin+)
/VIN_MOD: C1.1, C2.1, C3.1, C8.1, D1.1 (K), R1.2, TP2.1, U1.1 (VIN), U1.2 (EN), U1.14 (VIN), U2.8 (Vbus), U2.9 (Vin-)
/VIN_OR: D3.1 (K), D5.1 (K), F1.1, R8.1
/VPORT: D5.2 (A), J1.4, TP1.1
GND: C1.2, C2.2, C3.2, C4.2, C5.2, C6.2, C7.2, C8.2, C9.2, C10.2, C11.2, C12.2, C13.2, C14.2, C15.2, D1.2 (A), J1.3, J2.2, J3.1, J3.MP (MountPin), J6.2, J7.A1 (GND), J7.A12 (GND), J7.B1 (GND), J7.B12 (GND), J7.S1 (SHIELD), J9.2, LED1.1 (K), LED2.1 (K), LED3.1 (K), R4.2, R14.2, R15.2, SW1.2, SW2.2, TP5.1, TP6.1, U1.3 (NC), U1.10 (NC), U1.11 (NC), U1.12 (AGND), U1.15 (PGND), U2.1 (A1), U2.2 (A0), U2.7 (GND), U3.1 (A1), U3.7 (GND), U4.1 (GND), U4.2 (GND), U4.11 (GND), U4.14 (GND), U4.36 (GND), U4.37 (GND), U4.38 (GND), U4.39 (GND), U4.40 (GND), U4.41 (GND), U4.42 (GND), U4.43 (GND), U4.44 (GND), U4.45 (GND), U4.46 (GND), U4.47 (GND), U4.48 (GND), U4.49 (GND), U4.50 (GND), U4.51 (GND), U4.52 (GND), U4.53 (GND), U5.7 (GND), U6.2 (GND), U7.2 (GND)

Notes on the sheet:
1 POWER INPUT
D5 and D3 OR the two inputs. Either can be plugged in alone or both at once.
Meter the J1 pinout before the first plug-in. A wrong pinout can put battery on GND.
2 5 V REGULATOR
TPSM53602 set to 5.0 V: RFBT 10k, RFBB 2.49k (datasheet Table 7-1). 1.4 MHz fixed.
EN tied to VIN. AGND joins PGND at the module. Input 2 x 10u, output 2 x 47u.
6 ESP32-C3 MCU
USB-C is the built-in USB serial and JTAG port: flash and print over one cable.
Hold BOOT, tap RESET for download mode. R21, R22 hold the GPIO2 and GPIO8 straps high.
UART0 (GPIO20/21) is not broken out. USB-C is the console.
3 CURRENT SENSE
Route IN+ and IN- as Kelvin traces from the inside edge of each shunt pad.
Addresses: U2 0x40, U3 0x41, U5 0x45.
4 3.3 V REGULATOR
5V_LDO is fed by 5V through D2, or by USB through D4 and Q1.
Q1's gate sits on the 5 V rail: robot or bench power on turns Q1 off, so USB only carries data.
7 I2C, LEDS, OUTPUTS
5 USB-C
Separate 5.1k on each CC pin. USB D+/D- reach GPIO19/GPIO18 through 22 ohm R24, R25.
8 TEST POINTS, MECHANICAL
Test points are bare 3.4 x 1.8 mm copper pads, nothing to buy.
Same land as a Keystone 5015, so a loop can be soldered on later.
Power flags (tell ERC these nets are driven)
